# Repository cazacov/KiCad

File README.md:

# KiCad
My KiCad projects

## Setup
Environment variables:
- KICADLIB_SKISELEV - Path to Sergey Kiselev's KiCad library
- KICADLIB_VICTOR - Path to my KiCad library

### Symbol Libraries
- ${KICADLIB_SKISELEV}/library/my_components.kicad_sym
- ${KICADLIB_VICTOR}/symbols/VictorLib.kicad_sym

### Footprint Libraries
- ${KICADLIB_SKISELEV}/My_Components.pretty
- ${KICADLIB_VICTOR}/footprints/VictorLib.pretty

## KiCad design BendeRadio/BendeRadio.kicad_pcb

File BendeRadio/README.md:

# Benderadio

PCB for the [Benderadio](https://alexgyver.ru/benderadio/) project.

Improvements compared to original AlexGyver design
- Added LC-filters and capacitors on power lines
- Added JTAG IDC-socket
- Added LC-filters for speakers

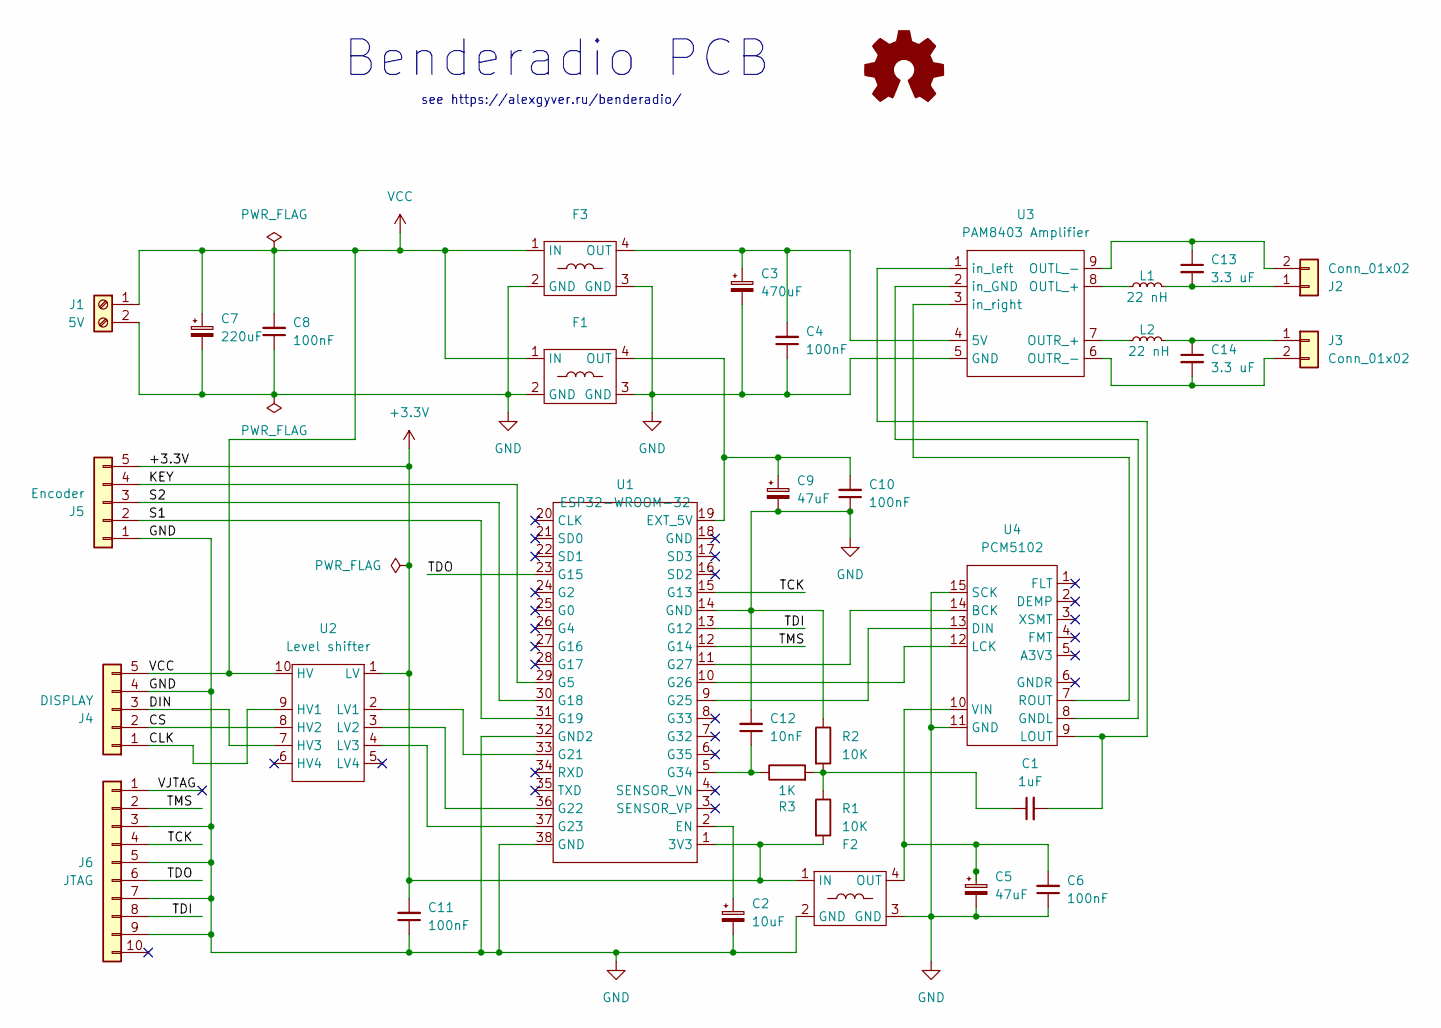
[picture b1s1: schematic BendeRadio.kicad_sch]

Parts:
C1: 1uF; C_Disc_D5.0mm_W2.5mm_P5.00mm
C2: 10uF; CP_Radial_Tantal_D4.5mm_P5.00mm
C3: 470uF; CP_Radial_D10.0mm_P3.80mm
C4, C6, C8, C10, C11: 100nF; C_1206_3216Metric
C5, C9: 47uF; CP_Radial_D6.3mm_P2.50mm
C7: 220uF; CP_Radial_D8.0mm_P3.50mm
C12: 10nF; C_1206_3216Metric
C13, C14: 3.3 uF; Cap_Cer_508
F1, F2, F3: LC-Filter
J1: 5V; TerminalBlock_bornier-2_P5.08mm
J2, J3: Conn_01x02; JST_EH_B2B-EH-A_1x02_P2.50mm_Vertical
J4: DISPLAY; JST_EH_B5B-EH-A_1x05_P2.50mm_Vertical
J5: Encoder; JST_EH_B5B-EH-A_1x05_P2.50mm_Vertical
J6: JTAG; IDC-Header_2x05_P2.54mm_Vertical
L1, L2: 22 nH; L_Axial_L6.6mm_D2.7mm_P2.54mm_Vertical_Vishay_IM-2
R1, R2: 10K; R_1206_3216Metric
R3: 1K; R_1206_3216Metric
U1: ESP32-WROOM-32; ESP32-DevBoard
U2: Level shifter; LevelShifter4
U3: PAM8403 Amplifier; PAM8403
U4: PCM5102

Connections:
+3.3V: C11.2, F2.1 (IN), J5.5, R1.2, U1.1 (3V3), U2.1 (LV)
/CLK: J4.1, U2.9 (HV1)
/CS: J4.2, U2.8 (HV2)
/DIN: J4.3, U2.7 (HV3)
/KEY: J5.4, U1.29 (G5)
/S1: J5.2, U1.31 (G19)
/S2: J5.3, U1.30 (G18)
/TCK: J6.4, U1.15 (G13)
/TDI: J6.8, U1.13 (G12)
/TDO: J6.6, U1.23 (G15)
/TMS: J6.2, U1.12 (G14)
/VJTAG: J6.1
GND: C2.2, C3.2, C4.1, C5.2, C6.1, C7.2, C8.1, C9.2, C10.1, C11.1, C12.2, F1.2 (GND), F1.3 (GND), F2.2 (GND), F2.3 (GND), F3.2 (GND), F3.3 (GND), J1.2, J4.4, J5.1, J6.3, J6.5, J6.7, J6.9, R2.1, U1.14 (GND), U1.32 (GND2), U1.38 (GND), U3.5 (GND), U4.11 (GND), U4.15 (SCK)
unnamed: C1.1, R1.1, R2.2, R3.2
unnamed: C9.1, C10.2, F1.4 (OUT), U1.19 (EXT_5V)
unnamed: C5.1, C6.2, F2.4 (OUT), U4.10 (VIN)
unnamed: C3.1, C4.2, F3.4 (OUT), U3.4 (5V)
unnamed: C13.2, J2.1, L1.2
unnamed: C13.1, J2.2, U3.9 (OUTL_-)
unnamed: C14.1, J3.1, L2.2
unnamed: C14.2, J3.2, U3.6 (OUTR_-)
unnamed: C2.1, U1.2 (EN)
unnamed: U1.33 (G21), U2.2 (LV1)
unnamed: U1.36 (G22), U2.3 (LV2)
unnamed: U1.37 (G23), U2.4 (LV3)
unnamed: U1.9 (G25), U4.13 (DIN)
unnamed: U1.10 (G26), U4.12 (LCK)
unnamed: U1.11 (G27), U4.14 (BCK)
unnamed: C12.1, R3.1, U1.5 (G34)
unnamed: L1.1, U3.8 (OUTL_+)
unnamed: L2.1, U3.7 (OUTR_+)
unnamed: U3.2 (in_GND), U4.8 (GNDL)
unnamed: C1.2, U3.1 (in_left), U4.9 (LOUT)
unnamed: U3.3 (in_right), U4.7 (ROUT)
VCC: C7.1, C8.2, F1.1 (IN), F3.1 (IN), J1.1, J4.5, U2.10 (HV)

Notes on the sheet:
see https://alexgyver.ru/benderadio/
Benderadio PCB

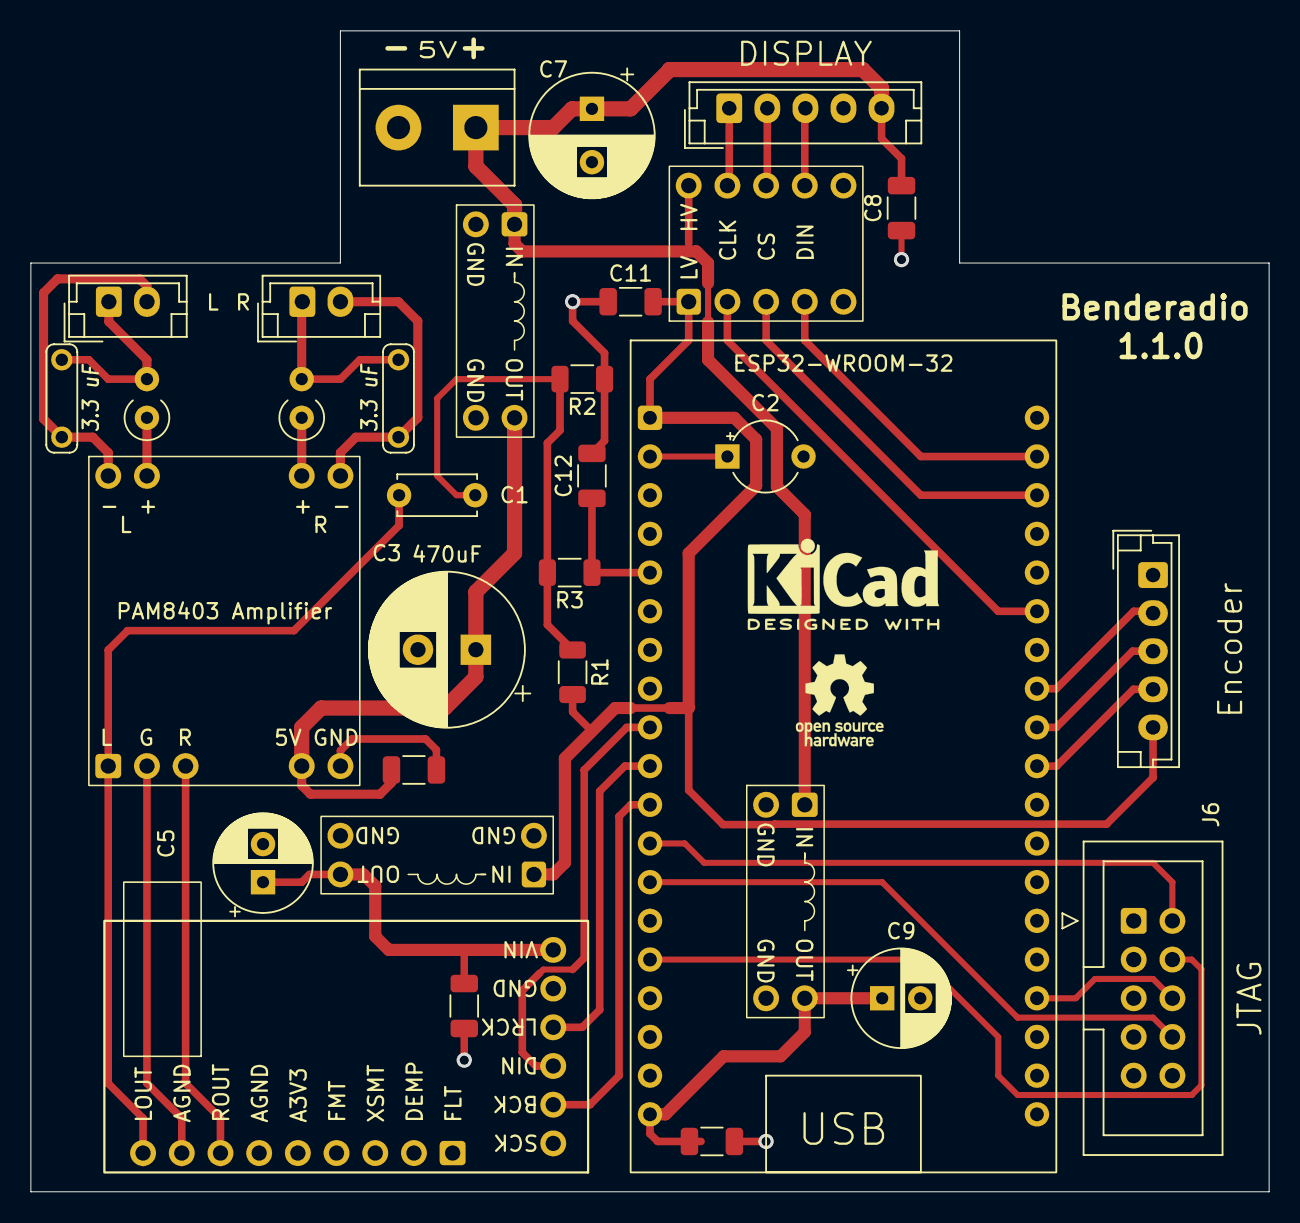
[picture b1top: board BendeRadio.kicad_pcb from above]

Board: 2 copper layers, 81.3 x 76.2 mm, 32 parts (0 on the bottom side), 34 nets.

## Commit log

2025-05-18 Benderadio project
2025-05-18 Revision 1.0.0
2025-10-11 BendeRadio 1.1.0
